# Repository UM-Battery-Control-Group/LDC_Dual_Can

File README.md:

# LDCquadCan
 can based LDC sensor

 Forgot to tie boot0 to ground so need to set nboot option in cube programmer

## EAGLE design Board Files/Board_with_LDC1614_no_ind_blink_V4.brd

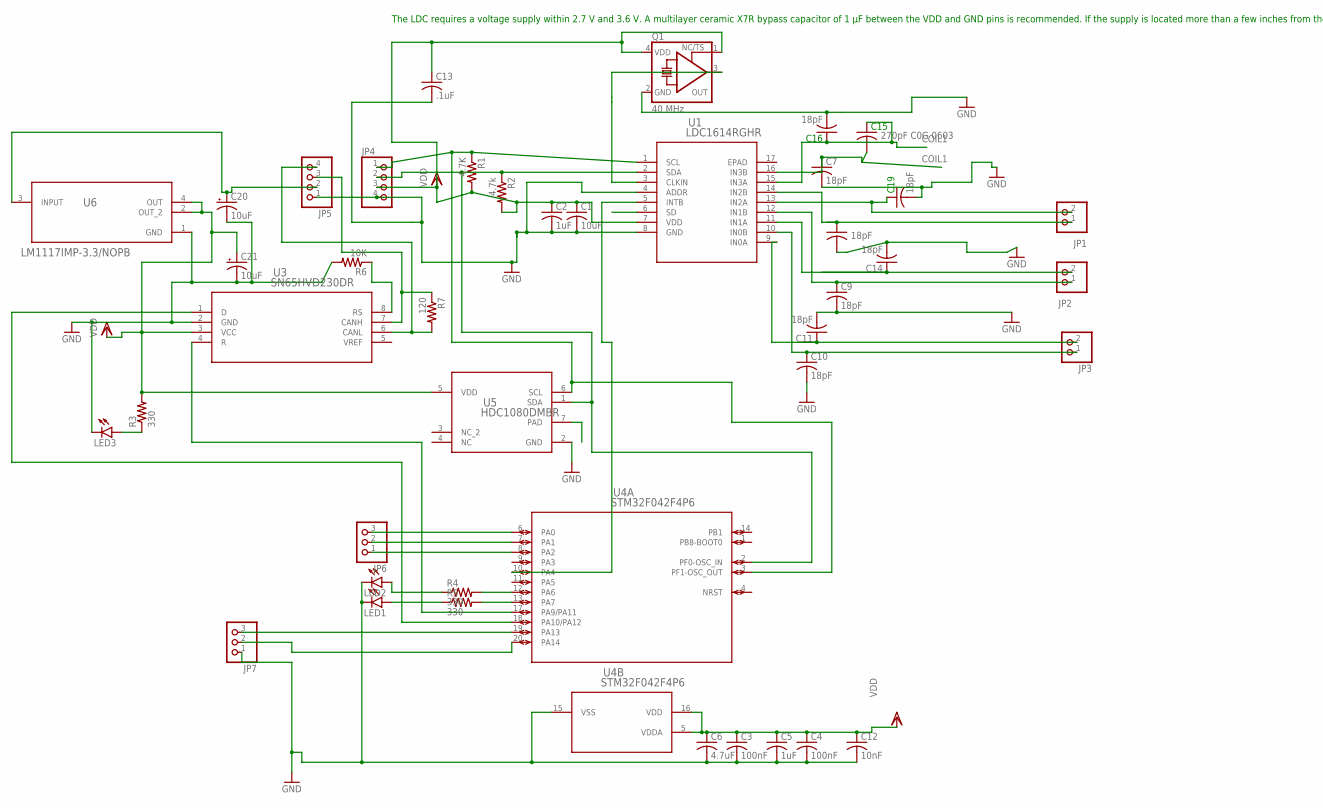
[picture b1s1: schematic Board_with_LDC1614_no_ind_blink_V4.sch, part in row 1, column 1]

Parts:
C1: 10uF; C0805
C2, C5: 1uF; C0805
C3, C4: 100nF; C0805
C6: 4.7uF; C0805
C7, C8, C9, C10, C11, C14, C16, C19: 18pF; C0805
C12: 10nF; C0805
C13: .1uF; C0805
C15: 270pF C0G 0603; C0805
C20, C21: 10uF; A/3216-18R
JP1, JP2, JP3: PINHD-1X2/90; 1X02/90
JP4, JP5: PINHD-1X4/90; 1X04/90
JP6, JP7: PINHD-1X3; 1X03
LED1, LED2, LED3: LEDSML0603; SML0603
Q1: 40 MHz; 2.5X2.0_KXO-V95; LCSC_PART C390542
R1: 4.7K; R0805
R2: 4.7k; R0805
R3, R4, R5: 330; R0603
R6: 10K; R0603
R7: 120; R0805
U1: LDC1614RGHR; RGH16_TEX
U3: SN65HVD230DR; D8
U4: STM32F042F4P6; TSSOP20
U5: HDC1080DMBR; DMB0006A
U6: LM1117IMP-3.3/NOPB; DCY0004A_N

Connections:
COIL1: C7.1, C15.1, C15.2, C16.1, U1.15 (IN3A), U1.16 (IN3B)
GND: C1.2, C2.2, C3.2, C4.2, C5.2, C6.2, C7.2, C8.2, C9.2, C10.2, C11.2, C12.2, C13.2, C14.2, C16.2, C19.2, C20.-, C21.-, JP4.4, JP5.1, JP7.1, LED1.C, LED2.C, LED3.C, Q1.2 (GND), R6.2, U1.4 (ADDR), U1.8 (GND), U3.2 (GND), U4.15 (VSS), U5.2 (GND), U6.1 (GND)
INTB: U1.5 (INTB), U4.10 (PA4)
unnamed: C20.+, JP5.2, U6.3 (INPUT)
unnamed: JP5.4, R7.2, U3.6 (CANL)
unnamed: JP5.3, R7.1, U3.7 (CANH)
unnamed: U3.1 (D), U4.18 (PA10/PA12)
unnamed: Q1.3 (OUT), U1.3 (CLKIN)
unnamed: R5.2, U4.13 (PA7)
unnamed: LED1.A, R5.1
unnamed: LED2.A, R4.1
unnamed: R4.2, U4.12 (PA6)
unnamed: LED3.A, R3.1
unnamed: U3.4 (R), U4.17 (PA9/PA11)
unnamed: C10.1, JP3.1, U1.10 (IN0B)
unnamed: C11.1, JP3.2, U1.9 (IN0A)
unnamed: JP7.2, U4.20 (PA14)
unnamed: C19.1, JP1.2, U1.13 (IN2A)
unnamed: C8.1, JP1.1, U1.14 (IN2B)
unnamed: C14.1, JP2.2, U1.11 (IN1A)
unnamed: C9.1, JP2.1, U1.12 (IN1B)
unnamed: JP6.3, U4.6 (PA0)
unnamed: JP7.3, U4.19 (PA13)
unnamed: R6.1, U3.8 (RS)
unnamed: JP6.2, U4.7 (PA1)
unnamed: JP6.1, U4.8 (PA2)
SCL: JP4.1, R1.1, U1.1 (SCL), U4.3 (PF1-OSC_OUT), U5.6 (SCL)
SD: U1.6 (SD)
SDA: JP4.2, R2.1, U1.2 (SDA), U4.2 (PF0-OSC_IN), U5.1 (SDA)
VDD: C1.1, C2.1, C3.1, C4.1, C5.1, C6.1, C12.1, C13.1, C21.+, JP4.3, Q1.1 (TS), Q1.4 (VDD), R1.2, R2.2, R3.2, U1.7 (VDD), U3.3 (VCC), U4.5 (VDDA), U4.16 (VDD), U5.5 (VDD), U6.2 (OUT_2), U6.4 (OUT)
VREF: U3.5 (VREF)

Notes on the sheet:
The LDC requires a voltage supply within 2.7 V and 3.6 V. A multilayer ceramic X7R bypass capacitor of 1 μF between the VDD and GND pins is recommended. If the supply is located more than a few inches from the LDC, additional capacitance may be required in addition to the ceramic bypass capacitor. 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

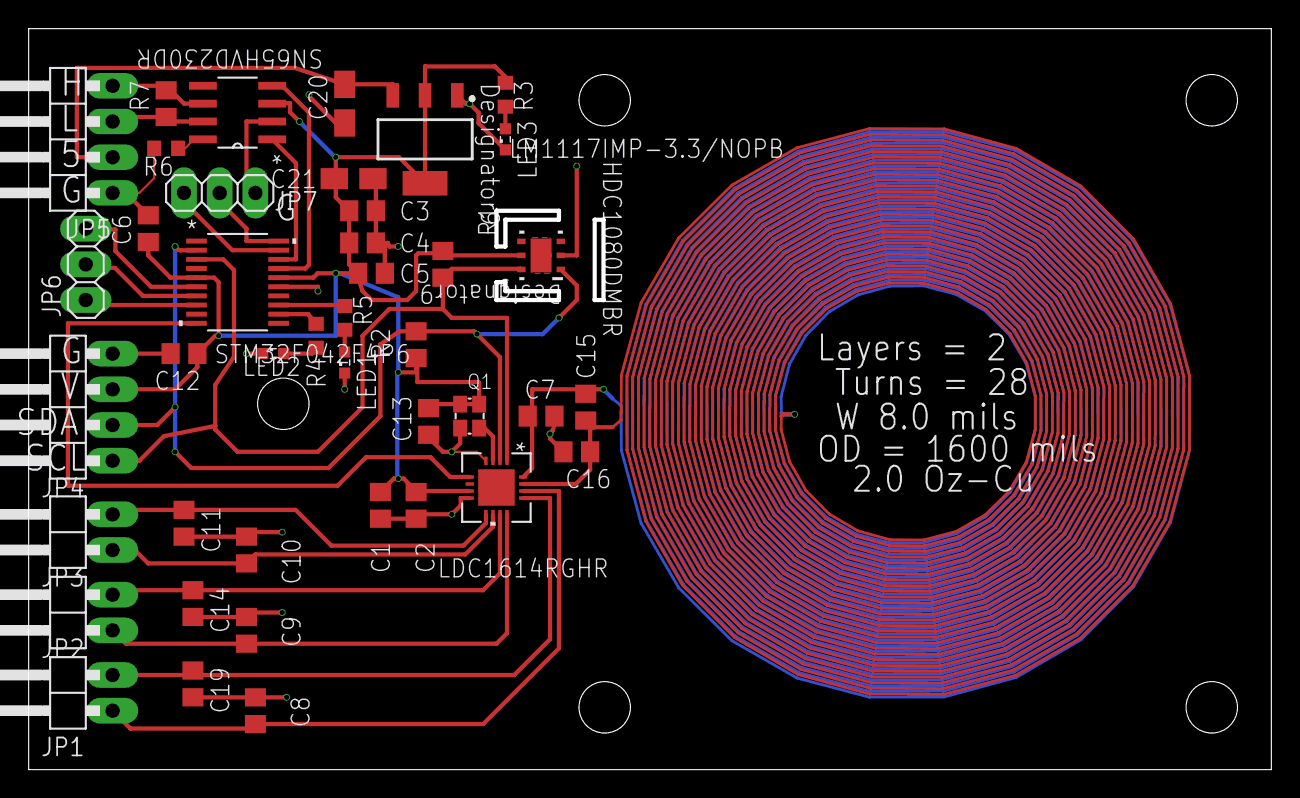
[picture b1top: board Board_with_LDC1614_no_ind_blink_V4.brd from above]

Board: 2 copper layers, 88.4 x 52.7 mm, 42 parts (0 on the bottom side), 29 nets.

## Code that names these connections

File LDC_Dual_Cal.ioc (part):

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Mcu.Name=STM32F042K(4-6)Tx
Mcu.Package=LQFP32
Mcu.UserName=STM32F042K6Tx
PA0.Mode=IN0
PA0.Signal=ADC_IN0
PA10.Mode=I2C
PA10.Signal=I2C1_SDA
PA11.Mode=CAN_Activate
PA11.Signal=CAN_RX
PA12.Mode=CAN_Activate
PA12.Signal=CAN_TX
PA13.Mode=Serial_Wire
PA13.Signal=SYS_SWDIO
PA14.Mode=Serial_Wire
PA14.Signal=SYS_SWCLK
PA4.GPIOParameters=GPIO_ModeDefaultEXTI
PA4.GPIO_ModeDefaultEXTI=GPIO_MODE_IT_FALLING
PA4.Signal=GPXTI4
PA6.Signal=GPIO_Output
PA7.Signal=GPIO_Output
PA9.Mode=I2C
PA9.Signal=I2C1_SCL
PF0-OSC_IN.Mode=HSE-External-Oscillator
PF0-OSC_IN.Signal=RCC_OSC_IN
PF1-OSC_OUT.Mode=HSE-External-Oscillator
PF1-OSC_OUT.Signal=RCC_OSC_OUT
RCC.SYSCLKFreq_VALUE=16000000
RCC.SYSCLKSource=RCC_SYSCLKSOURCE_PLLCLK
board=custom

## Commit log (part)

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2024-01-08 fist pass
    can blink an LED>
2024-01-26 tested working code for new Dual channel boards
    Need to check LDC configuration, and timing. but tested and seems to work,
    Using timer channel 3 for interrupt based sampling of the board.
2024-02-05 code and setting update
2024-02-12 updated code with can interrupts enabled
2024-02-14 removed space hogs
2024-02-14 more changes to local files
    agh
2024-02-14 remove asc logging
    removed asc logs
2024-02-15 fix sampling rate and N=50 samples
    fix sampling rate issue and N=50, potential overflow bug.
2026-05-11 Remove V1 board hardware and Add Ver 3.2 board hardware
    Remove V1 board hardware and Add Ver 3.2 board hardware
2026-05-13 change can bitrate to 125
    changed the can bitrate to 125k
2026-06-03 Add thermistor reading support in firmware and logger
2026-06-09 Set ADC sampling time to max (239.5 cyc)

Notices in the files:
parts and their libraries:
crystal-geyer_V1_0: Copyright: Geyer-Electronic
COPYRIGHT: Copyright (C) 2022 Ultra Librarian. All rights reserved.
